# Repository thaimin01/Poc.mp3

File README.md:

# Poc.mp3
A mp3 player that fit into your pocket. With expandable micro sd storage, cool analog and digital VU meter. An AUX output so everyone is happy. All on the esp32

I made this because I want a portable music player that can plays music without ads or wifi, just completely offline. Also, it's also a great project that helped me learn more about 4 layers pcb, smd soldering and component placements. Finally, it's a cool project that I have had in my mind for so long until I found out about hackclub and stardance, they fund the project for me for FREE!

Schematic

PCB

This has 8 buttons, including:

-5 buttons for navigation: Up, Down, Left, Right, Select

-2 buttons for volume changing: Volume up/down

-1 buttons for locking/unlocking

-Features and ESP32-S3 with 8MB of PSRAM and 16MB of flash (N16R8)

-Analog VU meter and two version of digital VU meter (NCS circle and Flat)

-Able to play pretty much most popular audio file with the ability to load the MP3 embeded images

-With SDMMC 1 bit can loads image and music up to 2MB/s (under ideal conditions)

-A 3.5mm jack output with full on Stereo

-Finally a full on UI with home screen and more !

Bill Of Materials

| Reference                       | Qty | Value                          | DNP | Exclude from BOM | Exclude from Board | Exclude from Simulation | Exclude from Position Files | Footprint                                                      | Datasheet                                                                                                                                   | Cost (USD) | Note                                                       | Purchase links                                                                                                                                                                                                                                                                                                                                                                       |                     |
|---------------------------------|-----|--------------------------------|-----|------------------|--------------------|-------------------------|-----------------------------|----------------------------------------------------------------|---------------------------------------------------------------------------------------------------------------------------------------------|------------|------------------------------------------------------------|--------------------------------------------------------------------------------------------------------------------------------------------------------------------------------------------------------------------------------------------------------------------------------------------------------------------------------------------------------------------------------------|---------------------|
| BT1                             | 1   | 3.7V                           |     |                  |                    |                         | ${EXCLUDE_FROM_POS_FILES}   | Connector_Wire:SolderWire-0.25sqmm_1x02_P4.2mm_D0.65mm_OD1.7mm |                                                                                                                                             | $2.00      | single                                                     | https://shopee.vn/Pin-Li-Po-3.7V-1000mAh-803040-(Li-Polymer)-cho-%C4%91i%E1%BB%87n-tho%E1%BA%A1i-loa-Bluetooth-%C4%91%E1%BB%8Bnh-v%E1%BB%8B-GPS-camera-h%C3%A0nh-tr%C3%ACnh.-Pin-d%C3%A0y-8mm-i.54915183.7719953465?extraParams=%7B%22display_model_id%22%3A426651964634%2C%22model_selection_logic%22%3A3%7D&image_ids=vn-11134207-7r98o-lzk1sn7hwv4xc1                             |                     |
| C1,C16,C18,C20,C24,C28          | 6   | 0.1uF                          |     |                  |                    |                         | ${EXCLUDE_FROM_POS_FILES}   | Capacitor_SMD:C_0603_1608Metric_Pad1.08x0.95mm_HandSolder      |                                                                                                                                             | $0.38      | (10pcs per strip)                                          | https://shopee.vn/T%E1%BB%A5-d%C3%A1n-0603-SMD-(10-con)-c%C3%A1c-tr%E1%BB%8B-s%E1%BB%91-1nF~10uF-i.85716713.2189388494?extraParams=%7B%22display_model_id%22%3A4100879982%2C%22model_selection_logic%22%3A3%7D&image_ids=d0fdae7238d4f778abf8ae27cd8fa5dc                                                                                                                            |                     |
| C2,C3,C4,C15,C17,C19,C23,C29    | 8   | 10uF                           |     |                  |                    |                         | ${EXCLUDE_FROM_POS_FILES}   | Capacitor_SMD:C_0805_2012Metric_Pad1.18x1.45mm_HandSolder      |                                                                                                                                             | $0.50      | (10pcs per strip)                                          | https://shopee.vn/T%E1%BB%A5-d%C3%A1n-0603-SMD-(10-con)-c%C3%A1c-tr%E1%BB%8B-s%E1%BB%91-1nF~10uF-i.85716713.2189388494?extraParams=%7B%22display_model_id%22%3A4100879982%2C%22model_selection_logic%22%3A3%7D&image_ids=d0fdae7238d4f778abf8ae27cd8fa5dc                                                                                                                            |                     |
| C5,C11                          | 2   | 22pF                           |     |                  |                    |                         | ${EXCLUDE_FROM_POS_FILES}   | Capacitor_SMD:C_0603_1608Metric_Pad1.08x0.95mm_HandSolder      |                                                                                                                                             | $0.38      | (10pcs per strip)                                          | https://shopee.vn/T%E1%BB%A5-d%C3%A1n-0603-(10-con)-c%C3%A1c-tr%E1%BB%8B-s%E1%BB%91-2.2pF~220pF-i.85716713.2189342367?extraParams=%7B%22display_model_id%22%3A4100692751%2C%22model_selection_logic%22%3A3%7D&image_ids=d696cad4bddcca09c8979b651e086f86                                                                                                                             |                     |
| C6,C7,C8,C9,C10,C12             | 6   | 22uF                           |     |                  |                    |                         | ${EXCLUDE_FROM_POS_FILES}   | Capacitor_SMD:C_0805_2012Metric_Pad1.18x1.45mm_HandSolder      |                                                                                                                                             | $1.50      | (50pcs per strip)                                          | https://shopee.vn/0805-(2012)-20-X5R-25V-22uF-T%E1%BB%A4-%C4%90I%E1%BB%86N-D%C3%81N-(-50PCS-T%C3%9AI-)-i.438929006.10008735991?extraParams=%7B%22display_model_id%22%3A35755380399%2C%22model_selection_logic%22%3A3%7D&image_ids=vn-11134207-7ra0g-m9i6dogk68av3a                                                                                                                   |                     |
| C13,C14,C30                     | 3   | 1uF                            |     |                  |                    |                         | ${EXCLUDE_FROM_POS_FILES}   | Capacitor_SMD:C_0603_1608Metric_Pad1.08x0.95mm_HandSolder      |                                                                                                                                             | $0.39      | (10pcs per strip)                                          | https://shopee.vn/T%E1%BB%A5-d%C3%A1n-0603-SMD-(10-con)-c%C3%A1c-tr%E1%BB%8B-s%E1%BB%91-1nF~10uF-i.85716713.2189388494?extraParams=%7B%22display_model_id%22%3A4100879982%2C%22model_selection_logic%22%3A3%7D&image_ids=d0fdae7238d4f778abf8ae27cd8fa5dc                                                                                                                            |                     |
| C21,C22                         | 2   | 2.2uF                          |     |                  |                    |                         | ${EXCLUDE_FROM_POS_FILES}   | Capacitor_SMD:C_0603_1608Metric_Pad1.08x0.95mm_HandSolder      |                                                                                                                                             | $0.77      | (50pcs per strip)                                          | https://shopee.vn/T%E1%BB%A5-g%E1%BB%91m-t%E1%BB%A5-d%C3%A1n-0603-(50c)-0.01uf-0.1uf-1uf-2.2uf-22uf-10uf-1nF-10nF-15nF-100pf-120nF-22pF-24pF-100pF-150pF-35-50V-gi%C3%A1-t%E1%BB%91t-i.298106917.57952938000?extraParams=%7B%22display_model_id%22%3A69955323146%2C%22model_selection_logic%22%3A3%7D&image_ids=vn-11134207-81ztc-mlx53y6j8w780f                                     |                     |
| C25,C26                         | 2   | 2.2nF                          |     |                  |                    |                         | ${EXCLUDE_FROM_POS_FILES}   | Capacitor_SMD:C_0603_1608Metric_Pad1.08x0.95mm_HandSolder      |                                                                                                                                             | $0.50      | (10pcs per strip)                                          | https://shopee.vn/T%E1%BB%A5-d%C3%A1n-0603-SMD-(10-con)-c%C3%A1c-tr%E1%BB%8B-s%E1%BB%91-1nF~10uF-i.85716713.2189388494?extraParams=%7B%22display_model_id%22%3A4100879982%2C%22model_selection_logic%22%3A3%7D&image_ids=d0fdae7238d4f778abf8ae27cd8fa5dc                                                                                                                            |                     |
| C27                             | 1   | 0.39uF                         |     |                  |                    |                         | ${EXCLUDE_FROM_POS_FILES}   | Capacitor_SMD:C_0603_1608Metric_Pad1.08x0.95mm_HandSolder      |                                                                                                                                             | $0.60      | (50pcs per strip)                                          | https://shopee.vn/0603-(1608)-10-X5R-50V-470nF-T%E1%BB%A4-%C4%90I%E1%BB%86N-D%C3%81N-(-50PCS-T%C3%9AI-)-i.438929006.3590816307?extraParams=%7B%22display_model_id%22%3A100478187982%2C%22model_selection_logic%22%3A3%7D&image_ids=vn-11134207-7ra0g-m9i6dogk68av3a                                                                                                                  |                     |
| C31,C32                         | 2   | 100nF                          |     |                  |                    |                         | ${EXCLUDE_FROM_POS_FILES}   | Capacitor_SMD:C_0603_1608Metric_Pad1.08x0.95mm_HandSolder      |                                                                                                                                             | $0.38      | (10pcs per strip)                                          | https://shopee.vn/T%E1%BB%A5-d%C3%A1n-0603-SMD-(10-con)-c%C3%A1c-tr%E1%BB%8B-s%E1%BB%91-1nF~10uF-i.85716713.2189388494?extraParams=%7B%22display_model_id%22%3A4100879982%2C%22model_selection_logic%22%3A3%7D&image_ids=d0fdae7238d4f778abf8ae27cd8fa5dc                                                                                                                            |                     |
| D1,D2                           | 2   | 1N4148W                        |     |                  |                    |                         | ${EXCLUDE_FROM_POS_FILES}   | Diode_SMD:D_SOD-123                                            | https://www.vishay.com/docs/85748/1n4148w.pdf                                                                                               | $0.74      | (50pcs per strip)                                          | https://shopee.vn/(50-200-chi%E1%BA%BFc)-1N4148W-T4-SOD-123-SMD-Transistor-B%E1%BB%99-ch%E1%BB%89nh-l%C6%B0u-nhanh-Diode-i.1834388203.46862777815?extraParams=%7B%22display_model_id%22%3A297725402463%2C%22model_selection_logic%22%3A3%7D&image_ids=sg-11134201-824ha-mpvayae5dr7k1a                                                                                               |                     |
| D3                              | 1   | SS34                           |     |                  |                    |                         | ${EXCLUDE_FROM_POS_FILES}   | Diode_SMD:D_SMA                                                | https://www.vishay.com/docs/88751/ss32.pdf                                                                                                  | $0.81      | (10pcs per strip)                                          | https://shopee.vn/-T%C3%BAi-10-Con-SS34-Diode-Schottky-1N5822-IN5822-3A-40V-Ch%C3%A2n-D%C3%A1n-Ch%E1%BA%A5t-L%C6%B0%E1%BB%A3ng-T%E1%BB%91t-5822-%C4%90i-%E1%BB%90t-Nhanh-i.1046874499.23252616840?extraParams=%7B%22display_model_id%22%3A306122213870%2C%22model_selection_logic%22%3A3%7D&image_ids=vn-11134207-7r98o-lkw15sngecp712                                               |                     |
| J1                              | 1   | USB_C_Receptacle_USB2.0_16P    |     |                  |                    |                         | ${EXCLUDE_FROM_POS_FILES}   | Connector_USB:USB_C_Receptacle_HRO_TYPE-C-31-M-12              | https://www.usb.org/sites/default/files/documents/usb_type-c.zip                                                                            | $0.87      | (5pcs per strip)                                           | https://www.lcsc.com/product-detail/C165948.html                                                                                                                                                                                                                                                                                                                                     |                     |
| J2                              | 1   | 1.8 inch TFT screen ST7735     |     |                  |                    |                         | ${EXCLUDE_FROM_POS_FILES}   | Connector_PinSocket_2.54mm:PinSocket_1x08_P2.54mm_Vertical     |                                                                                                                                             | $2.70      | single                                                     | https://shopee.vn/M%C3%B4-%C4%91un-m%C3%A0n-h%C3%ACnh-hi%E1%BB%83n-th%E1%BB%8B-%C4%91i%E1%BB%87n-t%E1%BB%AD-th%C3%B4ng-minh-NORMAN-SPI-TFT-LCD-kh%C3%B4ng-OLED-HD-65K-0.96-1.3-1.44-1.8-inch-hi%E1%BB%83n-th%E1%BB%8B-7P-i.578443443.15825397717?extraParams=%7B%22display_model_id%22%3A96369890214%2C%22model_selection_logic%22%3A3%7D&image_ids=1574962074877130f7853a365a959a1f |                     |
| J4                              | 1   | AudioJack3_SwitchTR            |     |                  |                    |                         | ${EXCLUDE_FROM_POS_FILES}   | Connector_Audio:Jack_3.5mm_CUI_SJ2-3593D-SMT_Horizontal        |                                                                                                                                             | $1.34      | single                                                     | https://www.mouser.com/en/ProductDetail/Same-Sky/SJ2-3593D-SMT-TR?qs=DXv0QSHKF4wWj2AnIqZJhQ%3D%3D                                                                                                                                                                                                                                                                                    |                     |
| J5                              | 1   | Micro_SD_Card_Det_Hirose_DM3AT |     |                  |                    |                         | ${EXCLUDE_FROM_POS_FILES}   | Connector_Card:microSD_HC_Hirose_DM3AT-SF-PEJM5                | https://www.hirose.com/product/en/download_file/key_name/DM3/category/Catalog/doc_file_id/49662/?file_category_id=4&item_id=195&is_series=1 | $3.50      | single                                                     | https://www.digikey.vn/en/products/detail/hirose-electric-co-ltd/DM3AT-SF-PEJM5(11)/4283091                                                                                                                                                                                                                                                                                          |                     |
| L1                              | 1   | 4.7 uH                         |     |                  |                    |                         | ${EXCLUDE_FROM_POS_FILES}   | Inductor_SMD:L_Taiyo-Yuden_NR-40xx_HandSoldering               |                                                                                                                                             | $2.00      | (10pcs per strip)                                          | https://vi.aliexpress.com/item/1005009861083201.html?spm=a2g0o.productlist.main.7.34e62cd7tBq0tg&algo_pvid=67c66b6b-01e2-4864-ac17-a98a379e45c6&pdp_ext_f=%7B%22order%22%3A%22275%22%2C%22eval%22%3A%221%22%2C%22fromPage%22%3A%22search%22%7D&utparam-url=scene%3Asearch%7Cquery_from%3A%7Cx_object_id%3A1005009861083201%7C_p_origin_prod%3A                                       |                     |
| L2                              | 1   | 2.2 uH                         |     |                  |                    |                         | ${EXCLUDE_FROM_POS_FILES}   | Inductor_SMD:L_Taiyo-Yuden_NR-40xx_HandSoldering               |                                                                                                                                             | $2.00      | (10pcs per strip)                                          | https://vi.aliexpress.com/item/1005009861083201.html?spm=a2g0o.productlist.main.7.34e62cd7tBq0tg&algo_pvid=67c66b6b-01e2-4864-ac17-a98a379e45c6&pdp_ext_f=%7B%22order%22%3A%22275%22%2C%22eval%22%3A%221%22%2C%22fromPage%22%3A%22search%22%7D&utparam-url=scene%3Asearch%7Cquery_from%3A%7Cx_object_id%3A1005009861083201%7C_p_origin_prod%3A                                       |                     |
| L3                              | 1   | 3.3uH                          |     |                  |                    |                         | ${EXCLUDE_FROM_POS_FILES}   | Inductor_SMD:L_Taiyo-Yuden_NR-40xx_HandSoldering               |                                                                                                                                             | $2.00      | (10pcs per strip)                                          | https://vi.aliexpress.com/item/1005009861083201.html?spm=a2g0o.productlist.main.7.34e62cd7tBq0tg&algo_pvid=67c66b6b-01e2-4864-ac17-a98a379e45c6&pdp_ext_f=%7B%22order%22%3A%22275%22%2C%22eval%22%3A%221%22%2C%22fromPage%22%3A%22search%22%7D&utparam-url=scene%3Asearch%7Cquery_from%3A%7Cx_object_id%3A1005009861083201%7C_p_origin_prod%3A                                       |                     |
| LS1                             | 1   | Speaker                        |     |                  |                    |                         | ${EXCLUDE_FROM_POS_FILES}   | Connector_Wire:SolderWire-0.25sqmm_1x02_P4.2mm_D0.65mm_OD1.7mm |                                                                                                                                             | $1.00      | single                                                     | https://shopee.vn/-Linh-Ki%E1%BB%87n-%C4%90i%E1%BB%87n-T%E1%BB%AD-G169-Loa-Mini-8-Ohm-1W-i.1774297521.43583004960?extraParams=%7B%22display_model_id%22%3A421279376656%2C%22model_selection_logic%22%3A3%7D&image_ids=vn-11134207-81ztc-mr5ace9bhh4xb7                                                                                                                               |                     |
| Q1                              | 1   | 2N7002                         |     |                  |                    |                         | ${EXCLUDE_FROM_POS_FILES}   | Package_TO_SOT_SMD:SOT-23                                      | https://www.onsemi.com/pub/Collateral/NDS7002A-D.PDF                                                                                        | $1.00      | (50pcs per strip)                                          | https://shopee.vn/50-100-C%C3%A1i-2N7002-MMBT7002-7002-SOT-23-60V-115mA-SMD-N-Channel-MOSFET-Transistor-i.1553543597.43753187122?extraParams=%7B%22display_model_id%22%3A305263160713%2C%22model_selection_logic%22%3A3%7D&image_ids=sg-11134201-7rd61-m7rk3yctjzqfa8                                                                                                                |                     |
| R1                              | 1   | 1K                             |     |                  |                    |                         | ${EXCLUDE_FROM_POS_FILES}   | Resistor_SMD:R_0603_1608Metric_Pad0.98x0.95mm_HandSolder       |                                                                                                                                             | $2.20      | (100pcs per strip)                                         | https://shopee.vn/100-Chi%E1%BA%BFc-%C4%90i%E1%BB%87n-Tr%E1%BB%9F-SMD-0402-0603-0805-1206-1K-2K-10K-20K-100K-200K-300K-910K-%C4%90i%E1%BB%87n-Tr%E1%BB%9F-Chip-i.1505927557.55565658564?extraParams=%7B%22display_model_id%22%3A254312816198%2C%22model_selection_logic%22%3A3%7D&image_ids=cn-11134207-820l4-mrl3q393dkhs6f                                                         |                     |
| R2                              | 1   | 0.05                           |     |                  |                    |                         | ${EXCLUDE_FROM_POS_FILES}   | Resistor_SMD:R_1206_3216Metric_Pad1.30x1.75mm_HandSolder       |                                                                                                                                             | $3.15      | (10pcs per strip)                                          | https://shopee.vn/5-c%C3%A1i-%C4%91i%E1%BB%87n-tr%E1%BB%9F-SMD-3W-2512-R015-R020-R025-R030-R040-R050-R100-R220-k%C3%ADch-th%C6%B0%E1%BB%9Bc-6.3x3.2mm-i.318023435.27012588521?extraParams=%7B%22display_model_id%22%3A395314202878%2C%22model_selection_logic%22%3A3%7D&image_ids=vn-11134207-7ras8-m43at1k2vrwn87                                                                   |                     |
| R3                              | 1   | 453K                           |     |                  |                    |                         | ${EXCLUDE_FROM_POS_FILES}   | Resistor_SMD:R_0603_1608Metric_Pad0.98x0.95mm_HandSolder       |                                                                                                                                             | $1.50      | (10pcs per strip)                                          | https://shopee.vn/100-chi%E1%BA%BFc-0402-0603-0805-1206-Chip-%C4%90i%E1%BB%87n-tr%E1%BB%9F-383K-390K-392K-402K-422K-430K-432K-442K-453K-464K-470K-Ohm-1--i.1434955377.56457947319?extraParams=%7B%22display_model_id%22%3A375705687067%2C%22model_selection_logic%22%3A3%7D&image_ids=51d71128a08b8bae6aab658ce58c2670                                                               |                     |
| R4                              | 1   | 100K                           |     |                  |                    |                         | ${EXCLUDE_FROM_POS_FILES}   | Resistor_SMD:R_0603_1608Metric_Pad0.98x0.95mm_HandSolder       |                                                                                                                                             | $2.20      | (100pcs per strip)                                         | https://shopee.vn/100-Chi%E1%BA%BFc-%C4%90i%E1%BB%87n-Tr%E1%BB%9F-SMD-0402-0603-0805-1206-1K-2K-10K-20K-100K-200K-300K-910K-%C4%90i%E1%BB%87n-Tr%E1%BB%9F-Chip-i.1505927557.55565658564?extraParams=%7B%22display_model_id%22%3A254312816198%2C%22model_selection_logic%22%3A3%7D&image_ids=cn-11134207-820l4-mrl3q393dkhs6f                                                         |                     |
| R5                              | 1   | 43K                            |     |                  |                    |                         | ${EXCLUDE_FROM_POS_FILES}   | Resistor_SMD:R_0603_1608Metric_Pad0.98x0.95mm_HandSolder       |                                                                                                                                             | $1.50      | (100pcs per strip)                                         | https://shopee.vn/Set-100-%C4%90i%E1%BB%87n-Tr%E1%BB%9F-M%E1%BA%A1ng-0603-8P4R-2-*-4P-5-22K-~-1M-ohm-30K-43K-100k-1M-Chuy%C3%AAn-D%E1%BB%A5ng-i.992251314.24456344500?extraParams=%7B%22display_model_id%22%3A204851952009%2C%22model_selection_logic%22%3A3%7D&image_ids=sg-11134202-7rbk3-llcyxp9xq8q457                                                                           |                     |
| R6                              | 1   | 440K                           |     |                  |                    |                         | ${EXCLUDE_FROM_POS_FILES}   | Resistor_SMD:R_0603_1608Metric_Pad0.98x0.95mm_HandSolder       |                                                                                                                                             | $1.00      | (100pcs per strip)                                         | https://shopee.vn/100-chi%E1%BA%BFc-0402-0603-0805-1206-Chip-%C4%90i%E1%BB%87n-tr%E1%BB%9F-383K-390K-392K-402K-422K-430K-432K-442K-453K-464K-470K-Ohm-1--i.1434955377.56457947319?extraParams=%7B%22display_model_id%22%3A375705687067%2C%22model_selection_logic%22%3A3%7D&image_ids=51d71128a08b8bae6aab658ce58c2670                                                               |                     |
| R7                              | 1   | 60K                            |     |                  |                    |                         | ${EXCLUDE_FROM_POS_FILES}   | Resistor_SMD:R_0603_1608Metric_Pad0.98x0.95mm_HandSolder       |                                                                                                                                             | $1.50      | (100pcs per strip)                                         | https://vi.aliexpress.com/item/1005005175276763.html?spm=a2g0o.productlist.main.2.31514ef0fWVJWM&algo_pvid=82eb29ea-e2eb-4fc6-bfdc-1e0ae692d968&pdp_ext_f=%7B%22order%22%3A%2220%22%2C%22eval%22%3A%221%22%2C%22fromPage%22%3A%22search%22%7D&utparam-url=scene%3Asearch%7Cquery_from%3A%7Cx_object_id%3A1005005175276763%7C_p_origin_prod%3A                                        |                     |
| R8,R9                           | 2   | 470                            |     |                  |                    |                         | ${EXCLUDE_FROM_POS_FILES}   | Resistor_SMD:R_0603_1608Metric_Pad0.98x0.95mm_HandSolder       |                                                                                                                                             | $1.00      | (100pcs per strip)                                         | https://shopee.vn/100-Chi%E1%BA%BFc-%C4%90i%E1%BB%87n-Tr%E1%BB%9F-SMD-0402-0603-0805-1206-1%CE%A9-10%CE%A9-100%CE%A9-200%CE%A9-470%CE%A9-560%CE%A9-680%CE%A9-910%CE%A9-%C4%90i%E1%BB%87n-Tr%E1%BB%9F-Chip-i.1505927557.54265654085?extraParams=%7B%22display_model_id%22%3A206421289517%2C%22model_selection_logic%22%3A3%7D&image_ids=cn-11134207-820l4-mrl3cr56slxd3a              |                     |
| R10                             | 1   | 20k                            |     |                  |                    |                         | ${EXCLUDE_FROM_POS_FILES}   | Resistor_SMD:R_0603_1608Metric_Pad0.98x0.95mm_HandSolder       |                                                                                                                                             | $1.00      | (100pcs per strip)                                         | https://shopee.vn/100-Chi%E1%BA%BFc-%C4%90i%E1%BB%87n-Tr%E1%BB%9F-SMD-0402-0603-0805-1206-1K-2K-10K-20K-100K-200K-300K-910K-%C4%90i%E1%BB%87n-Tr%E1%BB%9F-Chip-i.1505927557.55565658564?extraParams=%7B%22display_model_id%22%3A254312816198%2C%22model_selection_logic%22%3A3%7D&image_ids=cn-11134207-820l4-mrl3q393dkhs6f                                                         |                     |
| R11,R12                         | 2   | 1k                             |     |                  |                    |                         | ${EXCLUDE_FROM_POS_FILES}   | Resistor_SMD:R_0603_1608Metric_Pad0.98x0.95mm_HandSolder       |                                                                                                                                             | $1.00      | (100pcs per strip)                                         | https://shopee.vn/100-Chi%E1%BA%BFc-%C4%90i%E1%BB%87n-Tr%E1%BB%9F-SMD-0402-0603-0805-1206-1K-2K-10K-20K-100K-200K-300K-910K-%C4%90i%E1%BB%87n-Tr%E1%BB%9F-Chip-i.1505927557.55565658564?extraParams=%7B%22display_model_id%22%3A254312816198%2C%22model_selection_logic%22%3A3%7D&image_ids=cn-11134207-820l4-mrl3q393dkhs6f                                                         |                     |
| R13,R15,R16,R23,R24,R25,R26,R29 | 8   | 10k                            |     |                  |                    |                         | ${EXCLUDE_FROM_POS_FILES}   | Resistor_SMD:R_0603_1608Metric_Pad0.98x0.95mm_HandSolder       |                                                                                                                                             | $1.00      | (100pcs per strip)                                         | https://shopee.vn/100-Chi%E1%BA%BFc-%C4%90i%E1%BB%87n-Tr%E1%BB%9F-SMD-0402-0603-0805-1206-1K-2K-10K-20K-100K-200K-300K-910K-%C4%90i%E1%BB%87n-Tr%E1%BB%9F-Chip-i.1505927557.55565658564?extraParams=%7B%22display_model_id%22%3A254312816198%2C%22model_selection_logic%22%3A3%7D&image_ids=cn-11134207-820l4-mrl3q393dkhs6f                                                         |                     |
| R14,R17,R18,R27,R28,R30         | 6   | 100k                           |     |                  |                    |                         | ${EXCLUDE_FROM_POS_FILES}   | Resistor_SMD:R_0603_1608Metric_Pad0.98x0.95mm_HandSolder       |                                                                                                                                             | $1.00      | (100pcs per strip)                                         | https://shopee.vn/100-Chi%E1%BA%BFc-%C4%90i%E1%BB%87n-Tr%E1%BB%9F-SMD-0402-0603-0805-1206-1K-2K-10K-20K-100K-200K-300K-910K-%C4%90i%E1%BB%87n-Tr%E1%BB%9F-Chip-i.1505927557.55565658564?extraParams=%7B%22display_model_id%22%3A254312816198%2C%22model_selection_logic%22%3A3%7D&image_ids=cn-11134207-820l4-mrl3q393dkhs6f                                                         |                     |
| R19,R20                         | 2   | 5.1k                           |     |                  |                    |                         | ${EXCLUDE_FROM_POS_FILES}   | Resistor_SMD:R_0603_1608Metric_Pad0.98x0.95mm_HandSolder       |                                                                                                                                             | $1.00      | (100pcs per strip)                                         | https://shopee.vn/-0603-Tr%E1%BB%9F-d%C3%A1n-0603-tr%E1%BB%8B-s%E1%BB%91-t%E1%BB%AB-1K-%C4%91%E1%BA%BFn-9.9K-(g%C3%B3i-100-con)-i.72014335.7709700448?extraParams=%7B%22display_model_id%22%3A11047894552%2C%22model_selection_logic%22%3A3%7D&image_ids=vn-11134207-81ztc-mqko2e6nd4p957                                                                                            |                     |
| R31                             | 1   | 33                             |     |                  |                    |                         | ${EXCLUDE_FROM_POS_FILES}   | Resistor_SMD:R_0603_1608Metric_Pad0.98x0.95mm_HandSolder       |                                                                                                                                             | $1.00      | (100pcs per strip)                                         | https://shopee.vn/100-Chi%E1%BA%BFc-%C4%90i%E1%BB%87n-Tr%E1%BB%9F-SMD-0402-0603-0805-1206-1%CE%A9-10%CE%A9-100%CE%A9-200%CE%A9-470%CE%A9-560%CE%A9-680%CE%A9-910%CE%A9-%C4%90i%E1%BB%87n-Tr%E1%BB%9F-Chip-i.1505927557.54265654085?extraParams=%7B%22display_model_id%22%3A206421289517%2C%22model_selection_logic%22%3A3%7D&image_ids=cn-11134207-820l4-mrl3cr56slxd3a              |                     |
| SW1                             | 1   | Up                             |     |                  |                    |                         | ${EXCLUDE_FROM_POS_FILES}   | Button_Switch_SMD:SW_SPST_PTS645Sx43SMTR92                     |                                                                                                                                             |            |                                                            |                                                                                                                                                                                                                                                                                                                                                                                      |                     |
| SW2                             | 1   | Down                           |     |                  |                    |                         | ${EXCLUDE_FROM_POS_FILES}   | Button_Switch_SMD:SW_SPST_PTS645Sx43SMTR92                     |                                                                                                                                             |            |                                                            |                                                                                                                                                                                                                                                                                                                                                                                      |                     |
| SW3                             | 1   | Left                           |     |                  |                    |                         | ${EXCLUDE_FROM_POS_FILES}   | Button_Switch_SMD:SW_SPST_PTS645Sx43SMTR92                     |                                                                                                                                             |            |                                                            |                                                                                                                                                                                                                                                                                                                                                                                      |                     |
| SW4                             | 1   | Right                          |     |                  |                    |                         | ${EXCLUDE_FROM_POS_FILES}   | Button_Switch_SMD:SW_SPST_PTS645Sx43SMTR92                     |                                                                                                                                             |            |                                                            |                                                                                                                                                                                                                                                                                                                                                                                      |                     |
| SW5                             | 1   | Select                         |     |                  |                    |                         | ${EXCLUDE_FROM_POS_FILES}   | Button_Switch_SMD:SW_SPST_PTS645Sx43SMTR92                     |                                                                                                                                             | $0.60      | (20pcs per package)                                        | https://shopee.vn/-Stem-A-Z-125-Combo-20-Chi%E1%BA%BFc-N%C3%BAt-Nh%E1%BA%A5n-%C4%90%E1%BA%A7u-%C4%90%E1%BB%8F-4-Ch%C3%A2n-6x6x5-i.971933543.43407159150?extraParams=%7B%22display_model_id%22%3A290607066520%2C%22model_selection_logic%22%3A3%7D&image_ids=vn-11134207-7ras8-mbqjb7uohk6q46                                                                                         | THIS IS FOR BUTTONS |
| SW6                             | 1   | Volume +                       |     |                  |                    |                         | ${EXCLUDE_FROM_POS_FILES}   | Button_Switch_SMD:SW_SPST_PTS645Sx43SMTR92                     |                                                                                                                                             |            |                                                            |                                                                                                                                                                                                                                                                                                                                                                                      |                     |
| SW7                             | 1   | Volume -                       |     |                  |                    |                         | ${EXCLUDE_FROM_POS_FILES}   | Button_Switch_SMD:SW_SPST_PTS645Sx43SMTR92                     |                                                                                                                                             |            |                                                            |                                                                                                                                                                                                                                                                                                                                                                                      |                     |
| SW8                             | 1   | Lock/unlock                    |     |                  |                    |                         | ${EXCLUDE_FROM_POS_FILES}   | Button_Switch_SMD:SW_SPST_PTS645Sx43SMTR92                     |                                                                                                                                             |            |                                                            |                                                                                                                                                                                                                                                                                                                                                                                      |                     |
| SW9                             | 1   | Reset                          |     |                  |                    |                         | ${EXCLUDE_FROM_POS_FILES}   | Button_Switch_SMD:SW_SPST_EVQP2_MiddlePushTravel_H2.5mm        |                                                                                                                                             | $3.50      | (100pcs per bag)                                           | https://shopee.vn/Set-100-C%C3%B4ng-T%E1%BA%AFc-Nh%E1%BA%A5n-3*6-3*4-4*4-SMD-2Pin-4Pin-3x4x2-3x6x4.3-3x6x2.5-3x6x5-4x4x1.5*2.5-Ch%E1%BA%A5t-L%C6%B0%E1%BB%A3ng-Cao-i.165498337.21717326839?extraParams=%7B%22display_model_id%22%3A145016083575%2C%22model_selection_logic%22%3A3%7D&image_ids=19b11354d2dce49d4d2d47d1a3ead42b                                                      |                     |
| U1                              | 1   | XB6086A                        |     |                  |                    |                         | ${EXCLUDE_FROM_POS_FILES}   | Package_SO:SOIC-8-1EP_3.9x4.9mm_P1.27mm_EP2.29x3mm             |                                                                                                                                             | $1.00      |  (5pcs per strip)                                          | https://shopee.vn/10-5-Chi%E1%BA%BFc-Nguy%C3%AAn-B%E1%BA%A3n-XB8089D-XB8089G-XB8789D0-XB8608A-XB8608AJ-XB8886A-XB8887A-XB8606A-SOP8-ESOP8-SMD-IC-Qu%E1%BA%A3n-L%C3%BD-Ngu%E1%BB%93n-%C4%90i%E1%BB%87n-i.1553543597.43353172202?extraParams=%7B%22display_model_id%22%3A300262998010%2C%22model_selection_logic%22%3A3%7D&image_ids=sg-11134201-7renc-m8bnwduk3ezt94                  |                     |
| U2                              | 1   | TP5000X-4.2-ESOP8              |     |                  |                    |                         | ${EXCLUDE_FROM_POS_FILES}   | Package_SO:SOIC-8-1EP_3.9x4.9mm_P1.27mm_EP2.29x3mm             | TP5000X-4.2-ESOP8                                                                                                                           | $2.00      | (5pcs per package)                                         | https://vi.aliexpress.com/item/1005010278071877.html?spm=a2g0o.productlist.main.15.5a484eb4ShPEq2&algo_pvid=4d748827-354f-49a9-a50c-be1cbbfc0390&pdp_ext_f=%7B%22order%22%3A%22-1%22%2C%22eval%22%3A%221%22%2C%22fromPage%22%3A%22search%22%7D&utparam-url=scene%3Asearch%7Cquery_from%3A%7Cx_object_id%3A1005010278071877%7C_p_origin_prod%3A                                       |                     |
| U3                              | 1   | SY8089AAAC                     |     |                  |                    |                         | ${EXCLUDE_FROM_POS_FILES}   | footprints:SY8089AAAC_SGY                                      | SY8089AAAC                                                                                                                                  | $1.60      | (10pcs per strip)                                          | https://shopee.vn/10-C%C3%81I-SY8089AAAC-SOT23-5-SY8089-SOT-SY8089AAC-SY8089A-SY8088AAC-SY8088-SY8113BADC-SY8113-SY8120B1ABC-SY8120-SY8201ABC-SY8032ABC-Linh-ki%E1%BB%87n-%C4%91i%E1%BB%87n-t%E1%BB%AD-i.1274879032.26851965422?extraParams=%7B%22display_model_id%22%3A59430202324%2C%22model_selection_logic%22%3A3%7D&image_ids=sg-11134201-7rd5z-lvpmd1buaxsqb6                  |                     |
| U4                              | 1   | LM4871M                        |     |                  |                    |                         | ${EXCLUDE_FROM_POS_FILES}   | LM4871M:SOIC127P599X175-8N                                     |                                                                                                                                             | $1.40      | single                                                     | https://shopee.vn/B%E1%BB%99-10-Linh-Ki%E1%BB%87n-Khu%E1%BA%BFch-%C4%90%E1%BA%A1i-%C3%82m-Thanh-LM4871MX-LM4871-SOP8-SOP-4871-3W-i.832347222.23724801045?extraParams=%7B%22display_model_id%22%3A127400703147%2C%22model_selection_logic%22%3A3%7D&image_ids=sg-11134201-23020-cgvizeoxilnv98                                                                                        |                     |
| U5                              | 1   | ESP32-S3-WROOM-1               |     |                  |                    |                         | ${EXCLUDE_FROM_POS_FILES}   | RF_Module:ESP32-S3-WROOM-1                                     | https://www.espressif.com/sites/default/files/documentation/esp32-s3-wroom-1_wroom-1u_datasheet_en.pdf                                      | $7.50      | single                                                     | https://shopee.vn/M%C3%B4-%C4%90un-Ph%C3%A1t-Tri%E1%BB%83n-Hai-L%C3%B5i-esp32-s3-wroom-1-n16r8-n8r2-wifi-5.0-i.213820428.22060647983?extraParams=%7B%22display_model_id%22%3A245017457671%2C%22model_selection_logic%22%3A3%7D&image_ids=sg-11134201-7rbmc-lnwrr3a2d7s80c                                                                                                            |                     |
| U6                              | 1   | PCM5102A                       |     |                  |                    |                         | ${EXCLUDE_FROM_POS_FILES}   | Package_SO:TSSOP-20_4.4x6.5mm_P0.65mm                          | https://www.ti.com/lit/ds/symlink/pcm5102a.pdf                                                                                              | $2.75      | single                                                     | https://shopee.vn/5-C%C3%A1i-1-PCM5102-PCM5102A-PCM5102APWR-112dB-%C3%82m-Thanh-Stereo-DAC-Chip-IC-i.1156302552.27530784240?extraParams=%7B%22display_model_id%22%3A218348939236%2C%22model_selection_logic%22%3A3%7D&image_ids=sg-11134201-7rdxi-lzw1fyn55ysifc                                                                                                                     |                     |
| U7                              | 1   | FP6276B                        |     |                  |                    |                         | ${EXCLUDE_FROM_POS_FILES}   | Package_SO:SOIC-8-1EP_3.9x4.9mm_P1.27mm_EP2.29x3mm             |                                                                                                                                             | $2.50      | (2pcs package)                                             | https://shopee.vn/2-5PCS-FP5207-FP6276B-FP7208-FP6277-FP6293-FP6296-SOP-8-B%E1%BB%99-s%E1%BA%A1c-%C4%91i%E1%BB%87n-Chip-IC-SMD-i.1230861975.29308344772?extraParams=%7B%22display_model_id%22%3A246412711132%2C%22model_selection_logic%22%3A3%7D&image_ids=cn-11134207-7r98o-lz5ovp6po2hue6                                                                                         |                     |
| 4 Layers PCB                    | 5   | Boards                         |     |                  |                    |                         |                             |                                                                |                                                                                                                                             | $28.50     | Engineering fees and board fees are included ($25 + $3.50) | https://jlcpcb.com/                                                                                                                                                                                                                                                                                                                                                                  |                     |
| Stencil                         | 1   | Sheet                          |     |                  |                    |                         |                             |                                                                |                                                                                                                                             | $12.19     | Stencil and elctropolishing are included ($7.22 +  $4.97)  | https://jlcpcb.com/                                                                                                                                                                                                                                                                                                                                                                  |                     |
| Solder paste                    | 1   | Tube                           |     |                  |                    |                         |                             |                                                                |                                                                                                                                             | $3.00      | 20g per tubes                                              | https://shopee.vn/Thi%E1%BA%BFc-b%E1%BB%99t-cao-c%E1%BA%A5p-Mechani-Solder-Paste-XG-Z40-20G-d%E1%BA%A1ng-tu%C3%BDp-Sn63-Pb37-k%E1%BA%BFt-d%C3%ADnh-si%C3%AAu-t%E1%BB%91t-i.882465674.18073881832?extraParams=%7B%22display_model_id%22%3A183895898023%2C%22model_selection_logic%22%3A3%7D&image_ids=sg-11134201-23020-dvbp87v6jrnve9                                                |                     |
|                                 |     |                                |     |                  |                    |                         |                             |                                                                | Shipping fees for PCB + Stencil                                                                                                             | $9.00      |                                                            |                                                                                                                                                                                                                                                                                                                                                                                      |                     |
|                                 |     |                                |     |                  |                    |                         |                             |                                                                | TOTAL                                                                                                                                       | $120.95    |                                                            |                                                                                                                                                                                                                                                                                                                                                                                      |                     |

Cost

5pcs of 4 layers PCB: ~$28.50 / 736.554 VND (for 55.245mm x 102.133)

Total of the components and required materials: ~$120.95 / 3.125.589 VND

If you want to do 3d printing: ~$22.00 / 571.593 VND in ABS material

Total: $150 or 3.876.300 VND for the bare working module only / $172 or 4.444.824 VND for a case you design on your own

Get $160 - $182 / 4.135.040 VND - 4.703.608 VND, this give you some extra headroom to compensate for shipping fees

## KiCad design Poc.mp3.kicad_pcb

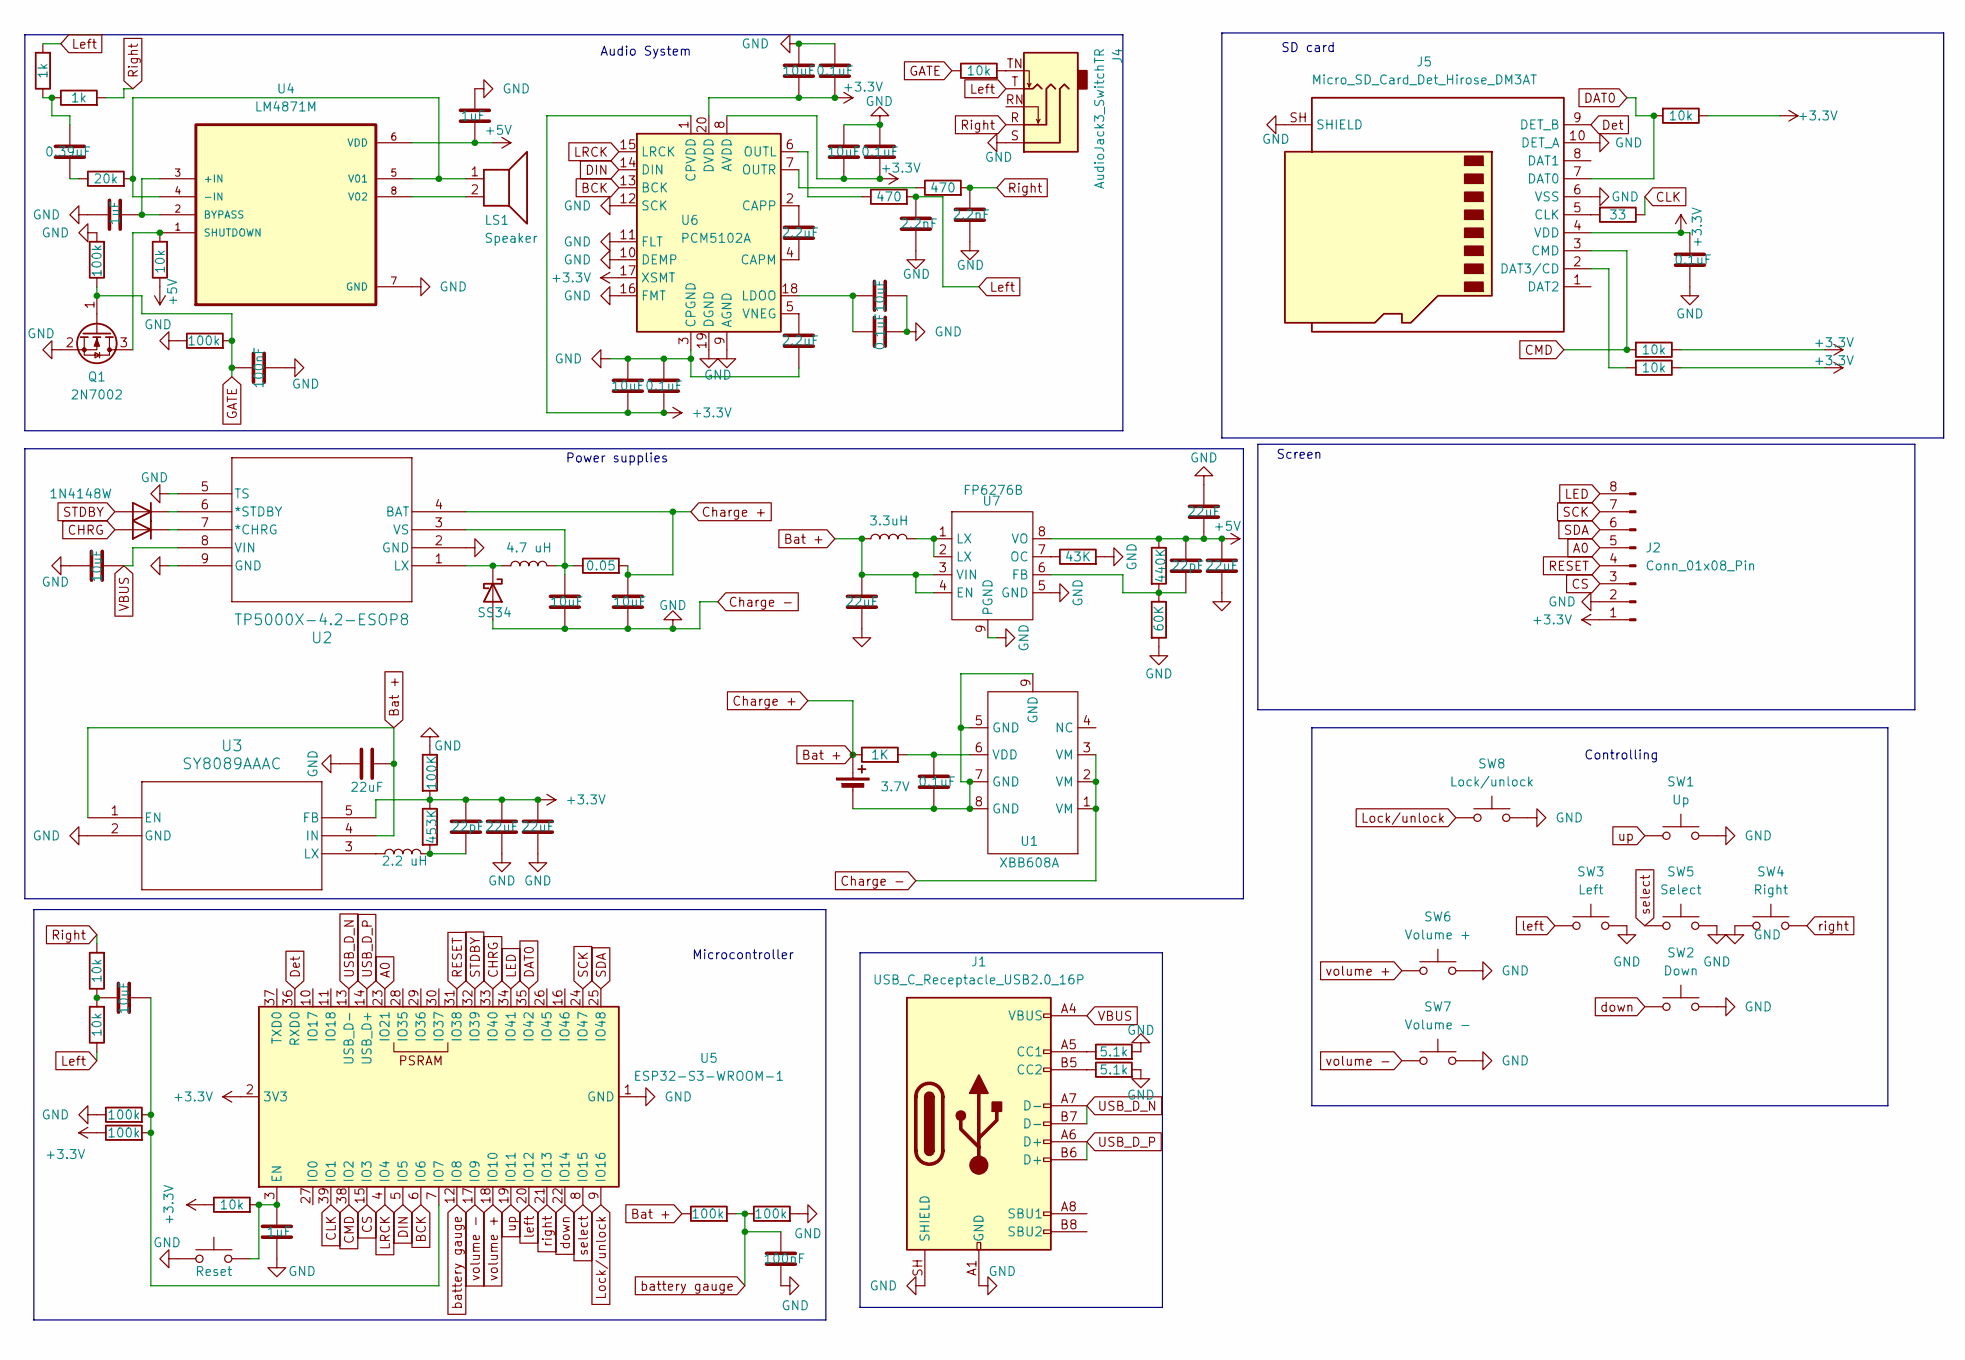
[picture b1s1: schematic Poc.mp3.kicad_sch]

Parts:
BT1: 3.7V; SolderWire-0.25sqmm_1x02_P4.2mm_D0.65mm_OD1.7mm
C1, C16, C18, C20, C24, C28: 0.1uF; C_0603_1608Metric_Pad1.08x0.95mm_HandSolder
C2, C3, C4, C15, C17, C19, C23, C29: 10uF; C_0805_2012Metric_Pad1.18x1.45mm_HandSolder
C5, C11: 22pF; C_0603_1608Metric_Pad1.08x0.95mm_HandSolder
C6, C7, C8, C9, C10, C12: 22uF; C_0805_2012Metric_Pad1.18x1.45mm_HandSolder
C13, C14, C30: 1uF; C_0603_1608Metric_Pad1.08x0.95mm_HandSolder
C21, C22: 2.2uF; C_0603_1608Metric_Pad1.08x0.95mm_HandSolder
C25, C26: 2.2nF; C_0603_1608Metric_Pad1.08x0.95mm_HandSolder
C27: 0.39uF; C_0603_1608Metric_Pad1.08x0.95mm_HandSolder
C31, C32: 100nF; C_0603_1608Metric_Pad1.08x0.95mm_HandSolder
D1, D2: 1N4148W; D_SOD-123
D3: SS34; D_SMA
J1: USB_C_Receptacle_USB2.0_16P; USB_C_Receptacle_HRO_TYPE-C-31-M-12
J2: Conn_01x08_Pin; PinSocket_1x08_P2.54mm_Vertical
J4: AudioJack3_SwitchTR; Jack_3.5mm_CUI_SJ2-3593D-SMT_Horizontal
J5: Micro_SD_Card_Det_Hirose_DM3AT; microSD_HC_Hirose_DM3AT-SF-PEJM5
L1: 4.7 uH; L_Taiyo-Yuden_NR-40xx_HandSoldering
L2: 2.2 uH; L_Taiyo-Yuden_NR-40xx_HandSoldering
L3: 3.3uH; L_Taiyo-Yuden_NR-40xx_HandSoldering
LS1: Speaker; SolderWire-0.25sqmm_1x02_P4.2mm_D0.65mm_OD1.7mm
Q1: 2N7002; SOT-23
R1: 1K; R_0603_1608Metric_Pad0.98x0.95mm_HandSolder
R2: 0.05; R_0603_1608Metric_Pad0.98x0.95mm_HandSolder
R3: 453K; R_0603_1608Metric_Pad0.98x0.95mm_HandSolder
R4: 100K; R_0603_1608Metric_Pad0.98x0.95mm_HandSolder
R5: 43K; R_0603_1608Metric_Pad0.98x0.95mm_HandSolder
R6: 440K; R_0603_1608Metric_Pad0.98x0.95mm_HandSolder
R7: 60K; R_0603_1608Metric_Pad0.98x0.95mm_HandSolder
R8, R9: 470; R_0603_1608Metric_Pad0.98x0.95mm_HandSolder
R10: 20k; R_0603_1608Metric_Pad0.98x0.95mm_HandSolder
R11, R12: 1k; R_0603_1608Metric_Pad0.98x0.95mm_HandSolder
R13, R15, R16, R23, R24, R25, R26, R29: 10k; R_0603_1608Metric_Pad0.98x0.95mm_HandSolder
R14, R17, R18, R27, R28, R30: 100k; R_0603_1608Metric_Pad0.98x0.95mm_HandSolder
R19, R20: 5.1k; R_0603_1608Metric_Pad0.98x0.95mm_HandSolder
R31: 33; R_0603_1608Metric_Pad0.98x0.95mm_HandSolder
SW1: Up; SW_SPST_PTS645Sx43SMTR92
SW2: Down; SW_SPST_PTS645Sx43SMTR92
SW3: Left; SW_SPST_PTS645Sx43SMTR92
SW4: Right; SW_SPST_PTS645Sx43SMTR92
SW5: Select; SW_SPST_PTS645Sx43SMTR92
SW6: Volume +; SW_SPST_PTS645Sx43SMTR92
SW7: Volume -; SW_SPST_PTS645Sx43SMTR92
SW8: Lock/unlock; SW_SPST_PTS645Sx43SMTR92
SW9: Reset; SW_SPST_EVQP2_MiddlePushTravel_H2.5mm
U1: XBB608A; SOIC-8-1EP_3.9x4.9mm_P1.27mm_EP2.29x3mm
U2: TP5000X-4.2-ESOP8; SOIC-8-1EP_3.9x4.9mm_P1.27mm_EP2.29x3mm
U3: SY8089AAAC; SY8089AAAC_SGY
U4: LM4871M; SOIC127P599X175-8N
U5: ESP32-S3-WROOM-1
U6: PCM5102A; TSSOP-20_4.4x6.5mm_P0.65mm
U7: FP6276B; SOIC-8-1EP_3.9x4.9mm_P1.27mm_EP2.29x3mm

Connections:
+3.3V: C5.2, C6.1, C8.1, C17.2, C18.2, C19.2, C20.2, C23.2, C24.2, C28.1, J2.1, J5.4 (VDD), R3.1, R4.2, R18.1, R23.1, R24.1, R25.1, R26.1, U3.5 (FB), U5.2 (3V3), U6.1 (CPVDD), U6.8 (AVDD), U6.17 (XSMT), U6.20 (DVDD)
+5V: C9.1, C10.1, C11.2, C14.1, R6.1, R13.1, U4.6 (VDD), U7.8 (VO)
A0: J2.5, U5.23 (IO21)
BCK: U5.6 (IO6), U6.13 (BCK)
Bat +: BT1.1 (+), C3.2, C7.2, C12.1, L3.1, R1.1, R2.2, R27.1, U2.4 (BAT), U3.1 (EN), U3.4 (IN), U7.3 (VIN), U7.4 (EN)
CHRG: D1.2 (A), U5.33 (IO40)
CLK: R31.1, U5.39 (IO1)
CMD: J5.3 (CMD), R23.2, U5.38 (IO2)
CS: J2.3, U5.15 (IO3)
Charge -: C2.1, C3.1, C4.1, C6.2, C7.1, C8.2, C9.2, C10.2, C12.2, C13.1, C14.2, C15.1, C16.1, C17.1, C18.1, C19.1, C20.1, C21.2, C23.1, C24.1, C25.2, C26.2, C28.2, C30.2, C31.2, C32.2, D3.2 (A), J1.A1 (GND), J1.A12 (GND), J1.B1 (GND), J1.B12 (GND), J1.SH (SHIELD), J2.2, J4.S, J5.6 (VSS), J5.10 (DET_A), J5.SH (SHIELD), Q1.2 (S), R4.1, R5.2, R7.2, R14.2, R17.1, R19.2, R20.2, R28.2, R30.1, SW1.2, SW2.2, SW3.2, SW4.1, SW5.2, SW6.2, SW7.2, SW8.2, SW9.1, U1.1 (VM), U1.2 (VM), U1.3 (VM), U2.2 (GND), U2.5 (TS), U2.9 (GND), U3.2 (GND), U4.7 (GND), U5.1 (GND), U5.40 (GND), U5.41 (GND), U6.3 (CPGND), U6.9 (AGND), U6.10 (DEMP), U6.11 (FLT), U6.12 (SCK), U6.16 (FMT), U6.19 (DGND), U7.5 (GND), U7.9 (PGND)
DAT0: J5.7 (DAT0), R24.2, U5.35 (IO42)
DIN: U5.5 (IO5), U6.14 (DIN)
Det: J5.9 (DET_B), U5.36 (RXD0)
GATE: C32.1, Q1.1 (G), R14.1, R29.1, R30.2
LED: J2.8, U5.34 (IO41)
LRCK: U5.4 (IO4), U6.15 (LRCK)
Left: C26.1, J4.T, R9.2, R11.2, R15.1
Lock/unlock: SW8.1, U5.9 (IO16)
unnamed: BT1.2 (-), C1.2, U1.5 (GND), U1.7 (GND), U1.8 (GND), U1.9 (GND)
unnamed: C5.1, L2.2, R3.2
unnamed: C27.1, R10.1
unnamed: C27.2, R11.1, R12.1
unnamed: C29.1, R15.2, R16.1
unnamed: D1.1 (K), U2.7 (*CHRG)
unnamed: D2.1 (K), U2.6 (*STDBY)
unnamed: D3.1 (K), L1.1, U2.1 (LX)
unnamed: J1.A5 (CC1), R19.1
unnamed: J1.B5 (CC2), R20.1
unnamed: J4.TN, R29.2
unnamed: J5.5 (CLK), R31.2
unnamed: J5.2 (DAT3/CD), R25.2
unnamed: L3.2, U7.1 (LX), U7.2 (LX)
unnamed: Q1.3 (D), R13.2, U4.1 (SHUTDOWN)
unnamed: C1.1, R1.2, U1.6 (VDD)
unnamed: C4.2, L1.2, R2.1, U2.3 (VS)
unnamed: L2.1, U3.3 (LX)
unnamed: C13.2, U4.2 (BYPASS), U4.3 (+IN)
unnamed: LS1.1, R10.2, U4.4 (-IN), U4.5 (V01)
unnamed: LS1.2, U4.8 (V02)
unnamed: C30.1, R26.2, SW9.2, U5.3 (EN)
unnamed: C29.2, R17.2, R18.2, U5.7 (IO7)
unnamed: C22.2, U6.4 (CAPM)
unnamed: C22.1, U6.2 (CAPP)
unnamed: C15.2, C16.2, U6.18 (LDOO)
unnamed: R9.1, U6.6 (OUTL)
unnamed: R8.1, U6.7 (OUTR)
unnamed: C21.1, U6.5 (VNEG)
unnamed: C11.1, R6.2, R7.1, U7.6 (FB)
unnamed: R5.1, U7.7 (OC)
RESET: J2.4, U5.31 (IO38)
Right: C25.1, J4.R, R8.2, R12.2, R16.2
SCK: J2.7, U5.24 (IO47)
SDA: J2.6, U5.25 (IO48)
STDBY: D2.2 (A), U5.32 (IO39)
USB_D_N: J1.A7 (D-), J1.B7 (D-), U5.13 (USB_D-)
USB_D_P: J1.A6 (D+), J1.B6 (D+), U5.14 (USB_D+)
VBUS: C2.2, J1.A4 (VBUS), J1.A9 (VBUS), J1.B4 (VBUS), J1.B9 (VBUS), U2.8 (VIN)
battery gauge: C31.1, R27.2, R28.1, U5.12 (IO8)
down: SW2.1, U5.22 (IO14)
left: SW3.1, U5.20 (IO12)
right: SW4.2, U5.21 (IO13)
select: SW5.1, U5.8 (IO15)
up: SW1.1, U5.19 (IO11)
volume +: SW6.1, U5.18 (IO10)
volume -: SW7.1, U5.17 (IO9)

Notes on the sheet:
Microcontroller
Audio System
SD card
Screen
Controlling
Power supplies

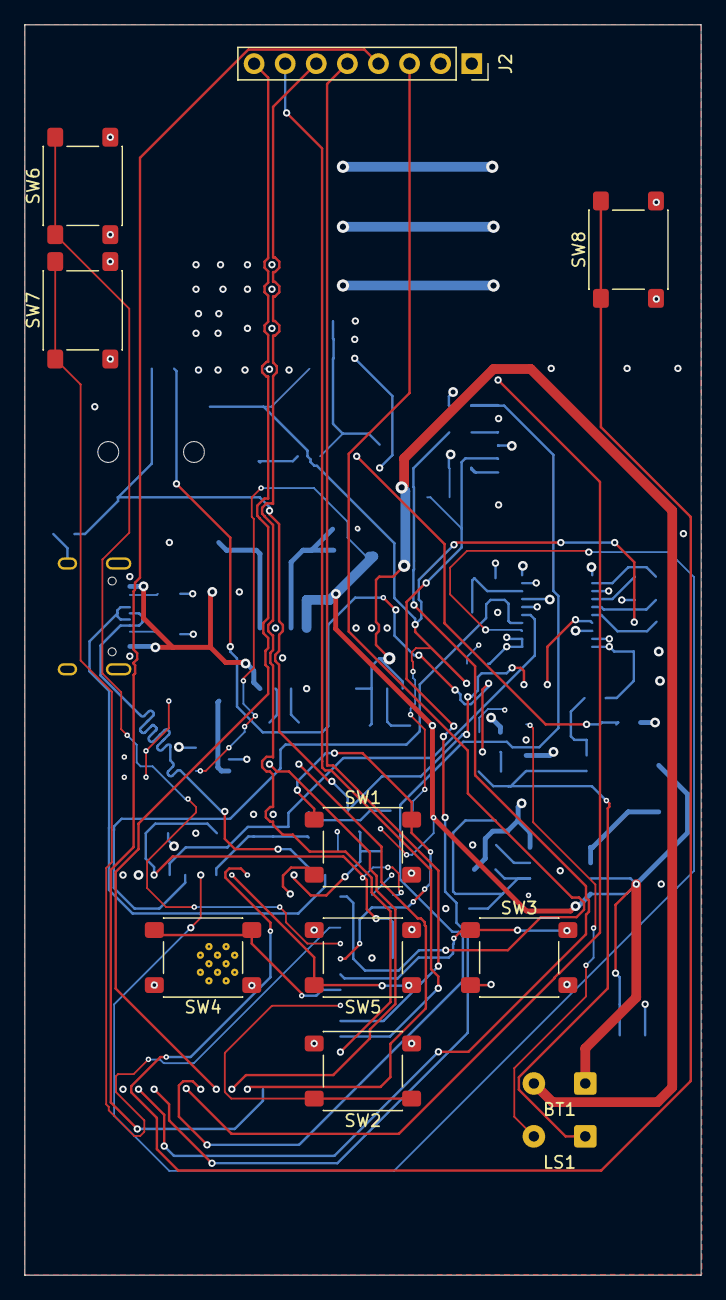
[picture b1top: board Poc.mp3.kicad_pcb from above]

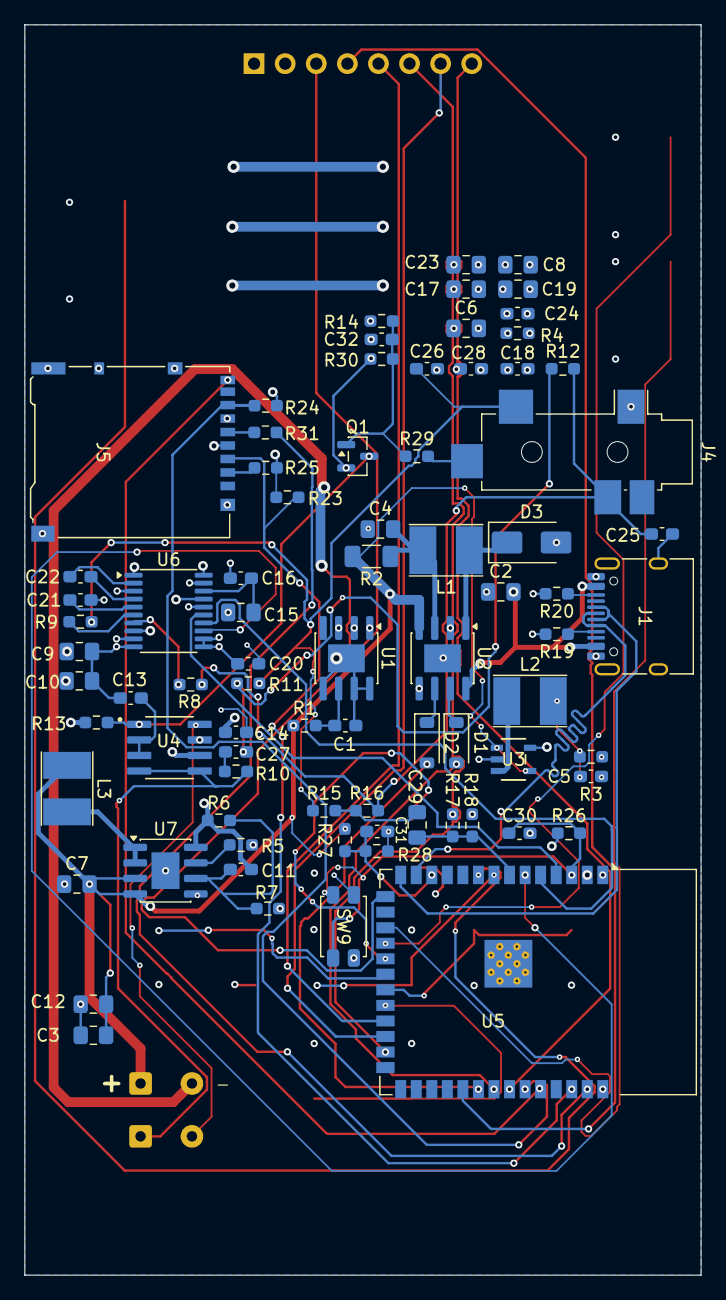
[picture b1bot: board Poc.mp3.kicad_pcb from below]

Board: 4 copper layers, 55.2 x 102.1 mm, 90 parts (79 on the bottom side), 65 nets.
